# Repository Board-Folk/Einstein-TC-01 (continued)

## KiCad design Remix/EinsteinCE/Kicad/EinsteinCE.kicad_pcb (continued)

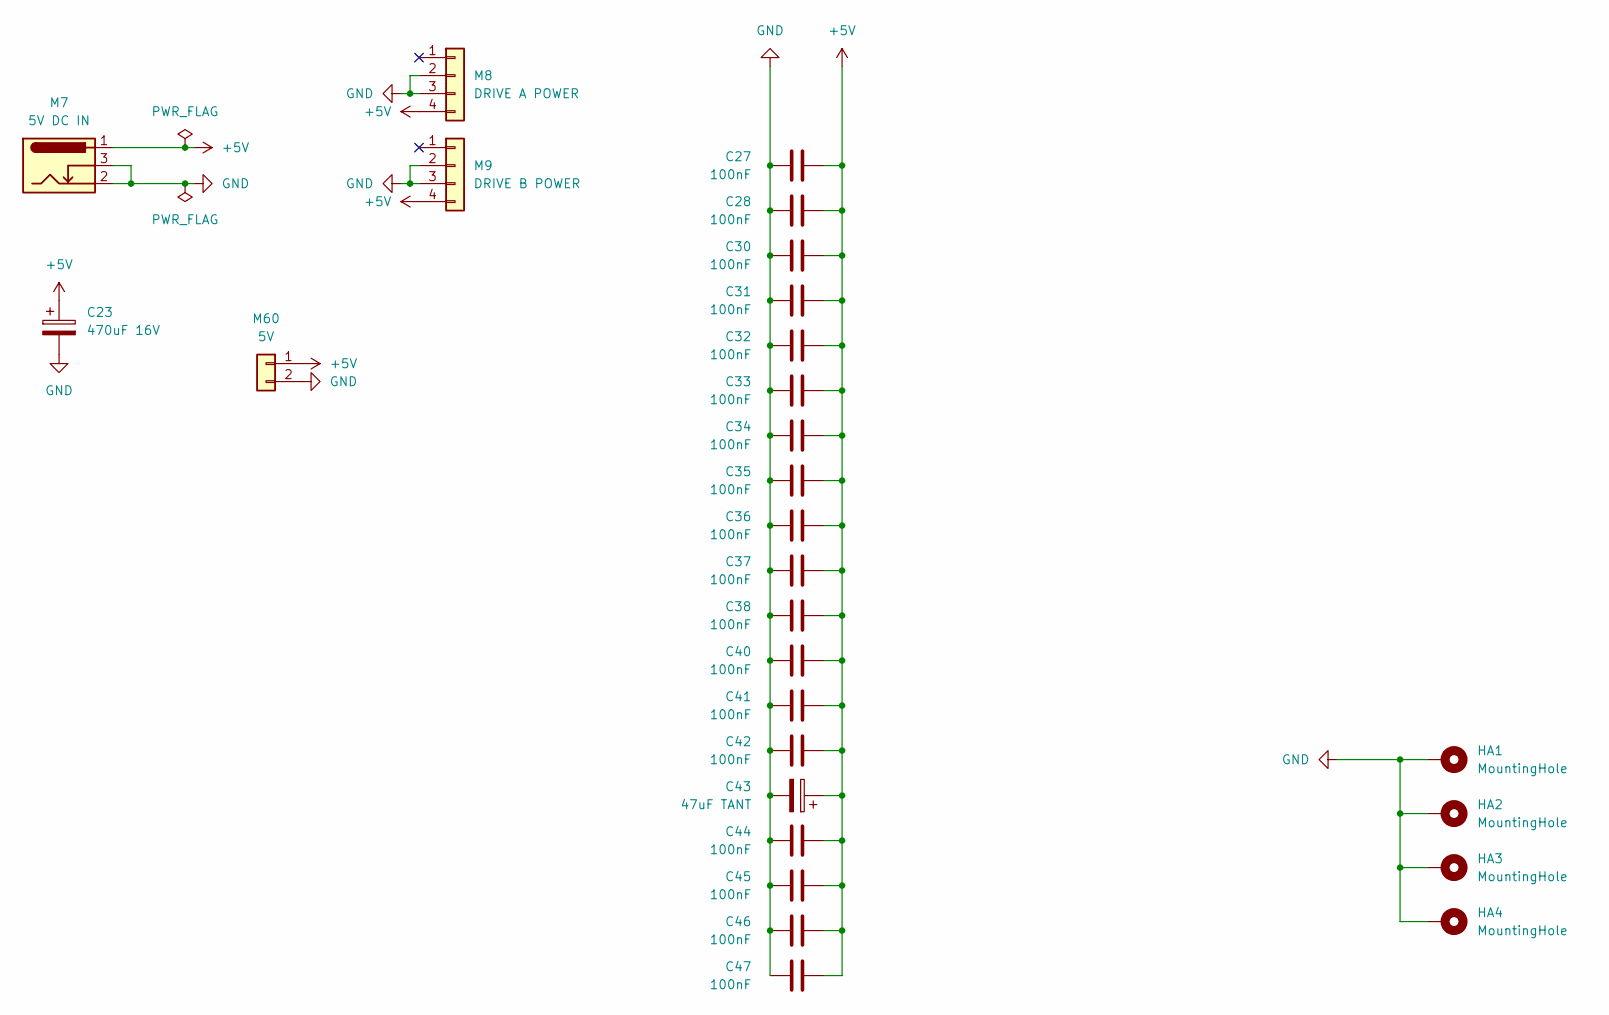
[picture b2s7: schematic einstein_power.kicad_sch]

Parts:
C23: 470uF 16V; Elec_5.08mm - Big Box
C27, C28, C30, C31, C32, C33, C34, C35, C36, C37, C38, C40, C41, C42, C44, C45, C46, C47: 100nF; C_Disc_5.08mm
C43: 47uF TANT; Elec_2.5mm - Box
HA1, HA2, HA3, HA4: MountingHole; Hole3.81_Pad_Via
M7: 5V DC IN; BarrelJack_Horizontal
M8: DRIVE A POWER; M10 PinHeader_1x04_P2.54mm
M9: DRIVE B POWER; M10 PinHeader_1x04_P2.54mm
M60: 5V; Power Header 3.96mm

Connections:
+5V: C23.1, C27.2, C28.2, C30.2, C31.2, C32.2, C33.2, C34.2, C35.2, C36.2, C37.2, C38.2, C40.2, C41.2, C42.2, C43.1, C44.2, C45.2, C46.2, C47.2, M7.1, M8.4, M9.4, M60.1; also elsewhere on the board
GND: C23.2, C27.1, C28.1, C30.1, C31.1, C32.1, C33.1, C34.1, C35.1, C36.1, C37.1, C38.1, C40.1, C41.1, C42.1, C43.2, C44.1, C45.1, C46.1, C47.1, HA1.1, HA2.1, HA3.1, HA4.1, M7.2, M7.3, M8.2, M8.3, M9.2, M9.3, M60.2; also elsewhere on the board

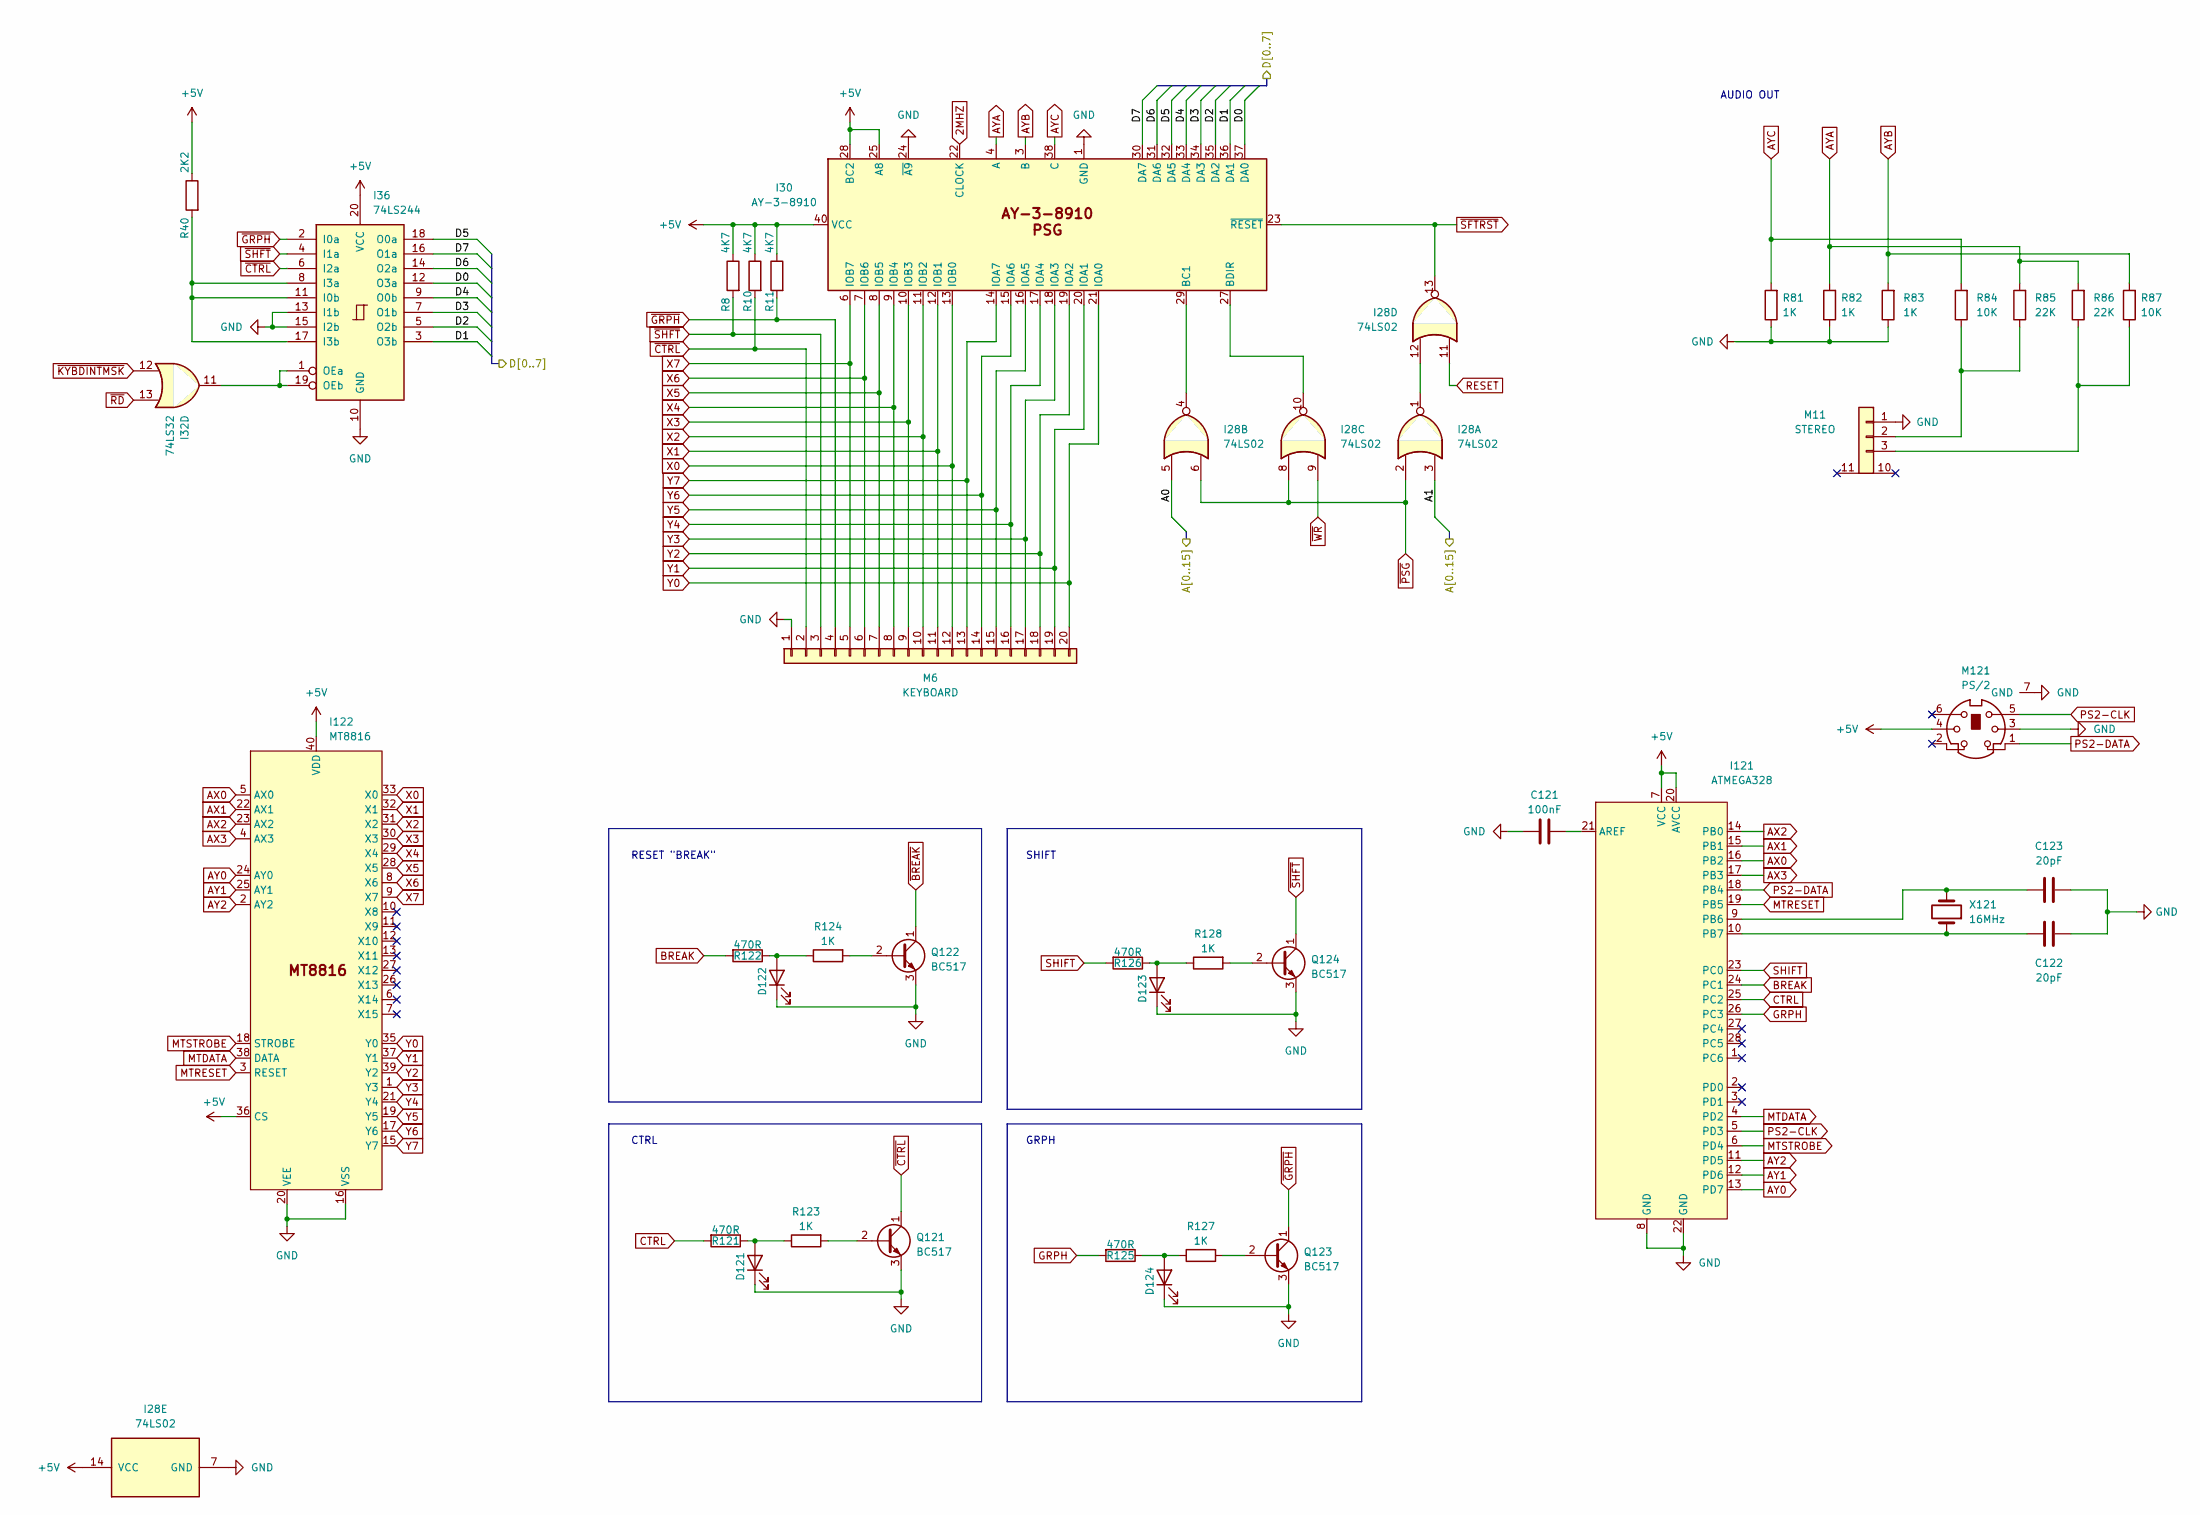
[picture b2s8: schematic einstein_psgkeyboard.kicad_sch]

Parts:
C121: 100nF; C_Disc_5.08mm
C122, C123: 20pF; C_Disc_2.54mm
D121: CTRL; LED_D3.0mm
D122: RESET; LED_D3.0mm
D123: SHIFT; LED_D3.0mm
D124: GRPH; LED_D3.0mm
I28: 74LS02; DIP-14_W7.62mm
I30: AY-3-8910; DIP-40_W15.24mm
I32: 74LS32; DIP-14_W7.62mm
I36: 74LS244; DIP-20_W7.62mm
I121: ATMEGA328; DIP-28_W7.62mm
I122: MT8816; DIP-40_W15.24mm
M6: KEYBOARD; Keyboard
M11: STEREO; Stereo_Jack
M121: PS/2; Connector_Mini-DIN_Female_6Pin_2rows
Q121, Q122, Q123, Q124: BC517; Transistor - Box 1 (Leg Rear)
R8, R10, R11: 4K7; Resistor 10.16mm
R40: 2K2; Resistor 10.16mm
R81, R82, R83: 1K; Resistor 10.16mm; LCSC C482939
R84, R87: 10K; Resistor 10.16mm; LCSC C84376
R85, R86: 22K; Resistor 10.16mm; LCSC C114565
R121, R122, R125, R126: 470R; Resistor 10.16mm
R123, R124, R127, R128: 1K; Resistor 10.16mm
X121: 16MHz; Crystal

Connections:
2MHZ: I30.22 (CLOCK); also elsewhere on the board
+5V: I28.14 (VCC), I30.25 (A8), I30.28 (BC2), I30.40 (VCC), I36.20 (VCC), I121.7 (VCC), I121.20 (AVCC), I122.36 (CS), I122.40 (VDD), M121.4, R8.1, R10.1, R11.1, R40.1; also elsewhere on the board
/Addressing/A0: I28.5; also elsewhere on the board
/Addressing/A1: I28.3; also elsewhere on the board
/CPU and Buffers/D0: I30.37 (DA0), I36.12 (O3a); also elsewhere on the board
/CPU and Buffers/D1: I30.36 (DA1), I36.3 (O3b); also elsewhere on the board
/CPU and Buffers/D2: I30.35 (DA2), I36.5 (O2b); also elsewhere on the board
/CPU and Buffers/D3: I30.34 (DA3), I36.7 (O1b); also elsewhere on the board
/CPU and Buffers/D4: I30.33 (DA4), I36.9 (O0b); also elsewhere on the board
/CPU and Buffers/D5: I30.32 (DA5), I36.18 (O0a); also elsewhere on the board
/CPU and Buffers/D6: I30.31 (DA6), I36.14 (O2a); also elsewhere on the board
/CPU and Buffers/D7: I30.30 (DA7), I36.16 (O1a); also elsewhere on the board
AX0: I121.16 (PB2), I122.5 (AX0)
AX1: I121.15 (PB1), I122.22 (AX1)
AX2: I121.14 (PB0), I122.23 (AX2)
AX3: I121.17 (PB3), I122.4 (AX3)
AY0: I121.13 (PD7), I122.24 (AY0)
AY1: I121.12 (PD6), I122.25 (AY1)
AY2: I121.11 (PD5), I122.2 (AY2)
AYA: I30.4 (A), R82.2, R85.2, R86.2
AYB: I30.3 (B), R83.2, R87.2
AYC: I30.38 (C), R81.2, R84.2
BREAK: I121.24 (PC1), R122.2
CTRL: I121.25 (PC2), R121.2
GND: C121.1, C122.2, C123.2, D121.1 (K), D122.1 (K), D123.1 (K), D124.1 (K), I28.7 (GND), I30.1 (GND), I30.24 (~A9), I36.10 (GND), I36.13 (I1b), I36.15 (I2b), I121.8 (GND), I121.22 (GND), I122.16 (VSS), I122.20 (VEE), M6.1, M11.1, M121.3, M121.7 (GND), Q121.3 (E), Q122.3 (E), Q123.3 (E), Q124.3 (E), R81.1, R82.1, R83.1; also elsewhere on the board
GRPH: I121.26 (PC3), R125.2
MTDATA: I121.4 (PD2), I122.38 (DATA)
MTRESET: I121.19 (PB5), I122.3 (RESET)
MTSTROBE: I121.6 (PD4), I122.18 (STROBE)
unnamed: D121.2 (A), R121.1, R123.1
unnamed: D122.2 (A), R122.1, R124.1
unnamed: D123.2 (A), R126.1, R128.1
unnamed: D124.2 (A), R125.1, R127.1
unnamed: I28.1, I28.12
unnamed: I28.4, I30.29 (BC1)
unnamed: I28.10, I30.27 (BDIR)
unnamed: I36.8 (I3a), I36.11 (I0b), I36.17 (I3b), R40.2
unnamed: I32.11, I36.1 (OEa), I36.19 (OEb)
unnamed: C121.2, I121.21 (AREF)
unnamed: C123.1, I121.9 (PB6), X121.2
unnamed: C122.1, I121.10 (PB7), X121.1
unnamed: M11.3 (Ground), R86.1, R87.1
unnamed: M11.2, R84.1, R85.1
unnamed: Q121.2 (B), R123.2
unnamed: Q122.2 (B), R124.2
unnamed: Q123.2 (B), R127.2
unnamed: Q124.2 (B), R128.2
PS2-CLK: I121.5 (PD3), M121.5
PS2-DATA: I121.18 (PB4), M121.1
RESET: I28.11; also elsewhere on the board
SHIFT: I121.23 (PC0), R126.2
X0: I30.13 (IOB0), I122.33 (X0), M6.12
X1: I30.12 (IOB1), I122.32 (X1), M6.11
X2: I30.11 (IOB2), I122.31 (X2), M6.10
X3: I30.10 (IOB3), I122.30 (X3), M6.9
X4: I30.9 (IOB4), I122.29 (X4), M6.8
X5: I30.8 (IOB5), I122.28 (X5), M6.7
X6: I30.7 (IOB6), I122.8 (X6), M6.6
X7: I30.6 (IOB7), I122.9 (X7), M6.5
Y0: I30.21 (IOA0), I122.35 (Y0), M6.20
Y1: I30.20 (IOA1), I122.37 (Y1), M6.19
Y2: I30.19 (IOA2), I122.39 (Y2), M6.18
Y3: I30.18 (IOA3), I122.1 (Y3), M6.17
Y4: I30.17 (IOA4), I122.21 (Y4), M6.16
Y5: I30.16 (IOA5), I122.19 (Y5), M6.15
Y6: I30.15 (IOA6), I122.17 (Y6), M6.14
Y7: I30.14 (IOA7), I122.15 (Y7), M6.13
~BREAK: Q122.1 (C); also elsewhere on the board
~CTRL: I36.6 (I2a), M6.2, Q121.1 (C), R10.2
~GRPH: I36.2 (I0a), M6.4, Q123.1 (C), R11.2
~KYBDINTMSK: I32.12; also elsewhere on the board
~PSG: I28.2, I28.6, I28.8; also elsewhere on the board
~RD: I32.13; also elsewhere on the board
~SFTRST: I28.13, I30.23 (~RESET); also elsewhere on the board
~SHFT: I36.4 (I1a), M6.3, Q124.1 (C), R8.2
~WR: I28.9; also elsewhere on the board

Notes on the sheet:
SHIFT
GRPH
CTRL
AUDIO OUT
RESET "BREAK"

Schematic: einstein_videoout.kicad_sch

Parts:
C81: 47nF; C_Disc_5.08mm
C82: 100uF; Elec_2.5mm - Box
L81: 10uH; Resistor 12.70mm
M81: COMPOSITE; RCA
Q81: BC549; Transistor - Box 1 (Leg Rear)
R88: 1K; Pot Straight
R89: 100R; Resistor 10.16mm
R90: 330R; Resistor 10.16mm

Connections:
+5V: L81.1; also elsewhere on the board
+5VL: C81.1, C82.1, L81.2, Q81.1 (C); also elsewhere on the board
GND: C81.2, C82.2, M81.2 (Ext), R89.2, R90.2; also elsewhere on the board
unnamed: M81.1 (In), Q81.3 (E), R90.1
unnamed: R88.2, R89.1
Y: Q81.2 (B), R88.1; also elsewhere on the board

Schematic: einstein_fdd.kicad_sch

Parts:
I34: 74LS02; DIP-14_W7.62mm
I42: WD1770; DIP-28_W15.24mm
I43: 74LS373; DIP-20_W7.62mm
I44, I45: 74LS38; DIP-14_W7.62mm
M4: EXTERNAL; PinHeader_2x17_P2.54mm; not fitted
M5: INTERNAL; PinHeader_2x17_P2.54mm
R27, R28, R30, R31: 220R; Resistor 10.16mm

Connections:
8MHZ: I42.18 (CLK); also elsewhere on the board
+5V: I42.15 (VCC), I43.20 (VCC), I44.14 (VCC), I45.14 (VCC), R27.1, R28.1, R30.1, R31.1; also elsewhere on the board
/Addressing/A0: I42.3 (A0); also elsewhere on the board
/Addressing/A1: I42.4 (A1); also elsewhere on the board
/CPU and Buffers/D0: I42.5 (DAL0), I43.3 (D0); also elsewhere on the board
/CPU and Buffers/D1: I42.6 (DAL1), I43.4 (D1); also elsewhere on the board
/CPU and Buffers/D2: I42.7 (DAL2), I43.7 (D2); also elsewhere on the board
/CPU and Buffers/D3: I42.8 (DAL3), I43.8 (D3); also elsewhere on the board
/CPU and Buffers/D4: I42.9 (DAL4), I43.13 (D4); also elsewhere on the board
/CPU and Buffers/D5: I42.10 (DAL5), I43.14 (D5); also elsewhere on the board
/CPU and Buffers/D6: I42.11 (DAL6), I43.17 (D6); also elsewhere on the board
/CPU and Buffers/D7: I42.12 (DAL7), I43.18 (D7); also elsewhere on the board
GND: I42.14 (GND), I42.26 (~DDEN), I43.1 (OE), I43.10 (GND), I44.7 (GND), I45.7 (GND), M4.1, M4.3, M4.5, M4.7, M4.9, M4.11, M4.13, M4.15, M4.17, M4.19, M4.21, M4.23, M4.25, M4.27, M4.29, M4.31, M4.33, M5.1, M5.3, M5.5, M5.7, M5.9, M5.11, M5.13, M5.15, M5.17, M5.19, M5.21, M5.23, M5.25, M5.27, M5.29, M5.31, M5.33; also elsewhere on the board
unnamed: I42.17 (DIRC), I44.9, I44.10
unnamed: I42.20 (MO), I45.1, I45.4, I45.9, I45.10
unnamed: I42.16 (STEP), I44.12, I44.13
unnamed: I42.22 (WD), I44.1, I44.2
unnamed: I42.21 (WG), I44.4, I44.5
unnamed: I34.10, I43.11 (LE)
unnamed: I43.2 (O0), I45.2
unnamed: I43.5 (O1), I45.5
unnamed: I43.12 (O4), I45.12, I45.13
fDIR: I44.8, M4.18, M5.18
fDRIVE0: I45.3, M4.10, M5.10
fDRIVE1: I45.6, M4.12, M5.12
fDRIVE2: M4.14, M5.14
fDRIVE3: M4.6, M5.6
fINDEX: I42.24 (~IP), M4.8, M5.8, R30.2
fMOTOR1: I45.8, M4.16, M5.16
fREAD: I42.19 (~RD), M4.30, M5.30, R31.2
fSIDE1: I45.11, M4.32, M5.32
fSTEP: I44.11, M4.20, M5.20
fTRACK0: I42.23 (~TR00), M4.26, M5.26, R27.2
fWDATA: I44.3, M4.22, M5.22
fWGATE: I44.6, M4.24, M5.24
fWRITEPROT: I42.25 (~WPRT), M4.28, M5.28, R28.2
~DRSEL: I34.8; also elsewhere on the board
~FDC: I42.1 (~CS); also elsewhere on the board
~SFTRST: I42.13 (~MR); also elsewhere on the board
~WR: I34.9, I42.2 (R~W); also elsewhere on the board

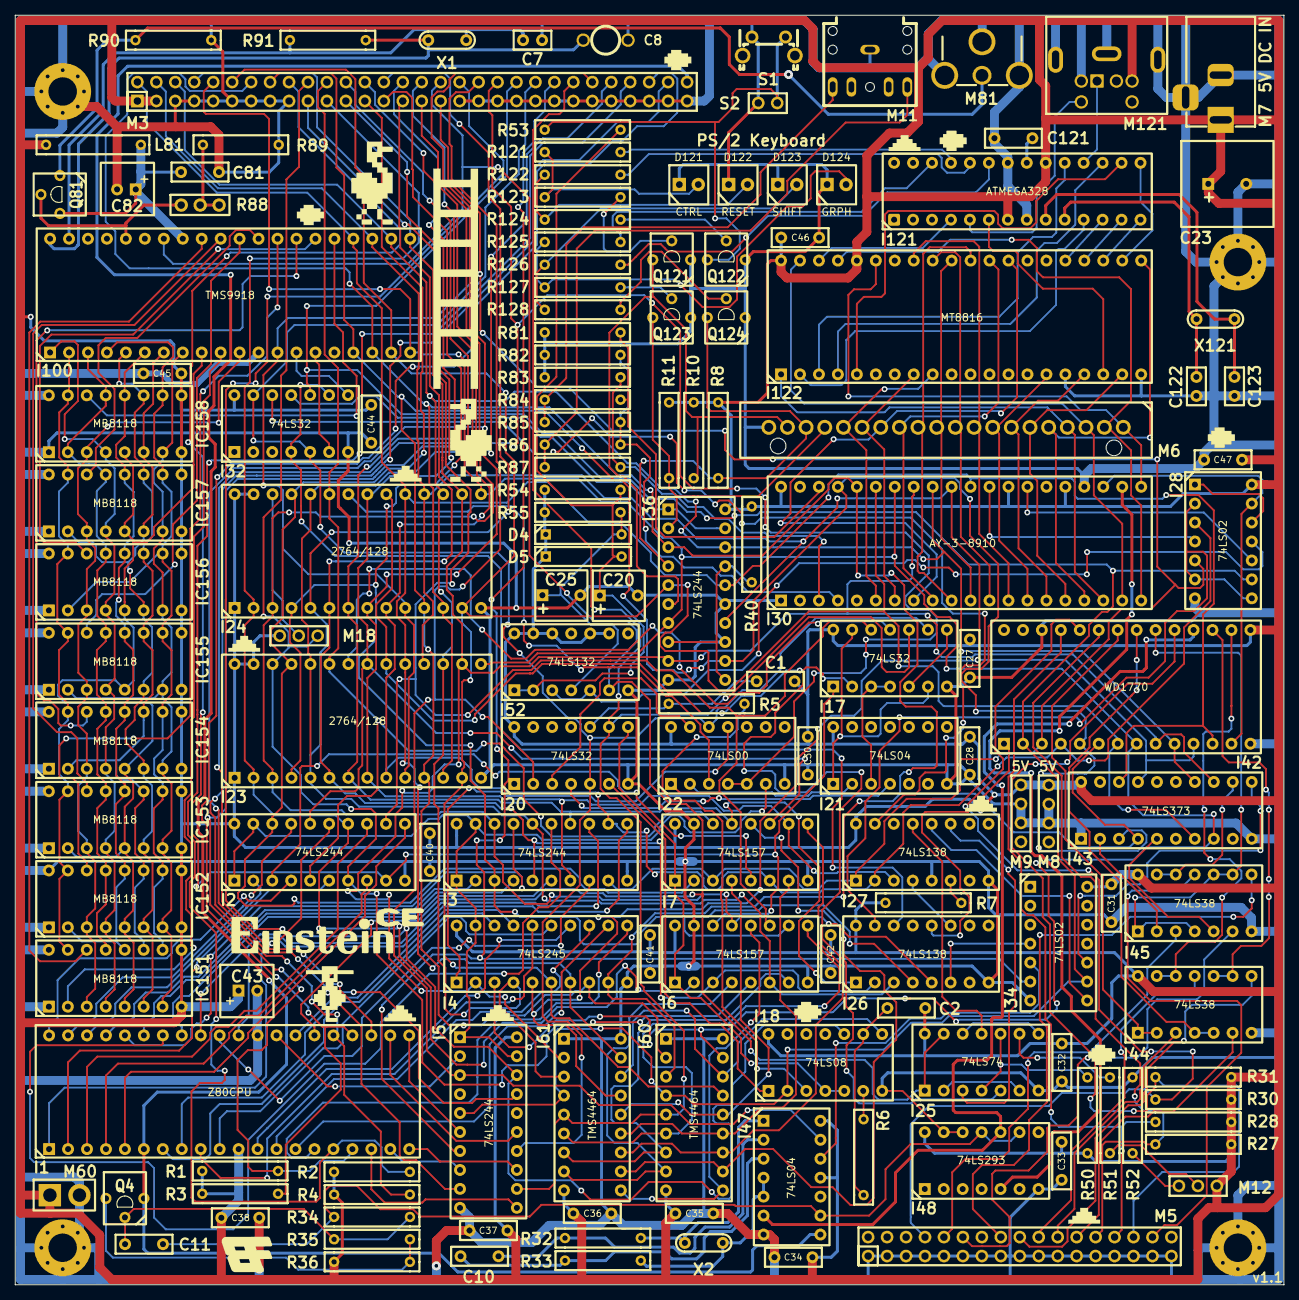
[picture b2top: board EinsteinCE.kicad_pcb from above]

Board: 2 copper layers, 170.0 x 170.1 mm, 174 parts (1 on the bottom side), 233 nets.

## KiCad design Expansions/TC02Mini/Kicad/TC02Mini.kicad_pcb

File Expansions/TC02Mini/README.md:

# Einstein TC-02Mini 80 Column Adapter

A simple, non-replica (schematics the same) remake of the TC-02 80 column board. Could be mounted on a ribbon cable, or as pictured on PC104 pin sockets (at full stretch). Required Character ROM at I4 in CHARROM folder. Please see the original manual for instructions for use.

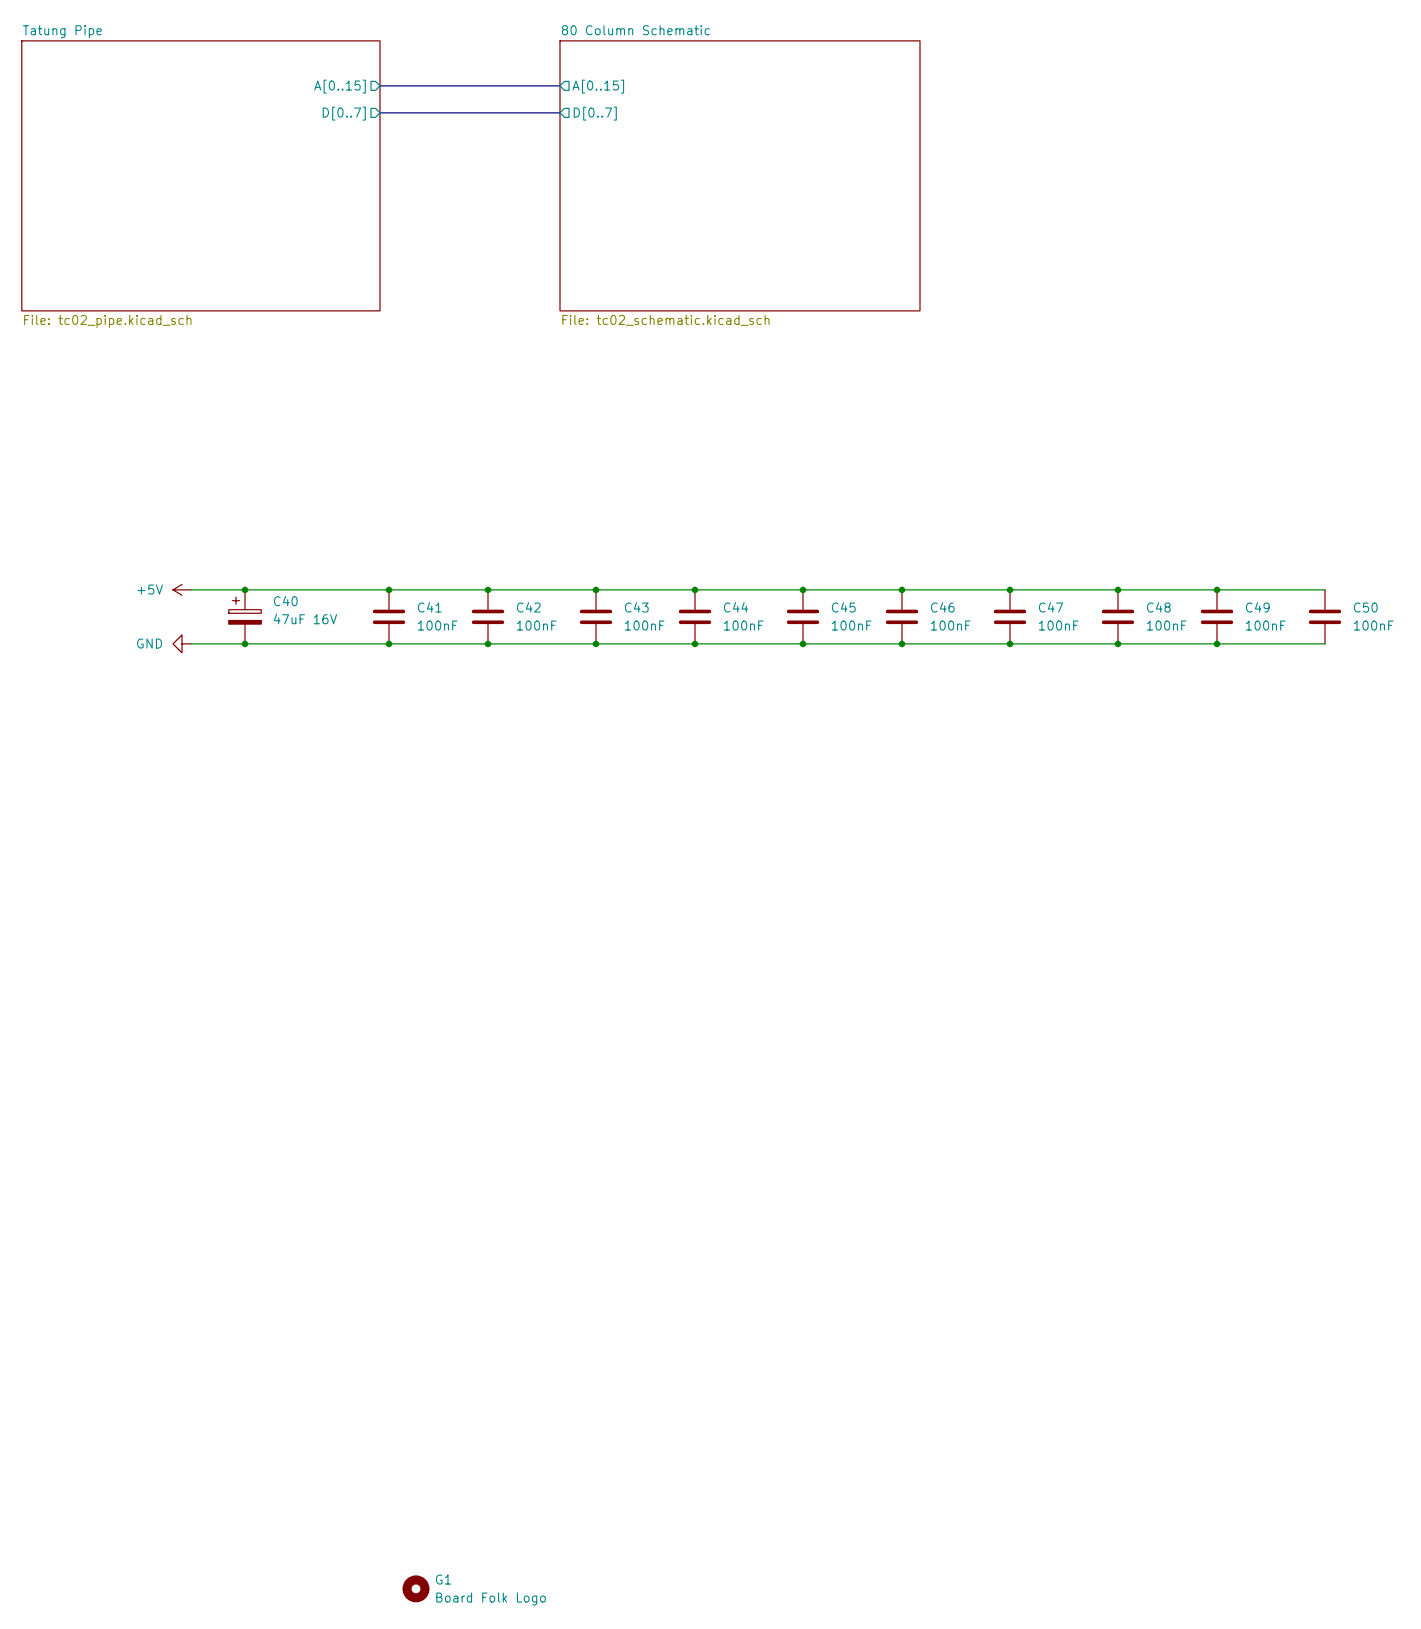
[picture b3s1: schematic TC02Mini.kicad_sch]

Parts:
C40: 47uF 16V; Elec_5.08mm - No Box
C41, C42, C43, C44, C45, C46, C47, C48, C49, C50: 100nF; C_Disc_5.08mm
G1: Board Folk Logo; BF12

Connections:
+5V: C40.1, C41.1, C42.1, C43.1, C44.1, C45.1, C46.1, C47.1, C48.1, C49.1, C50.1; also elsewhere on the board
GND: C40.2, C41.2, C42.2, C43.2, C44.2, C45.2, C46.2, C47.2, C48.2, C49.2, C50.2; also elsewhere on the board
